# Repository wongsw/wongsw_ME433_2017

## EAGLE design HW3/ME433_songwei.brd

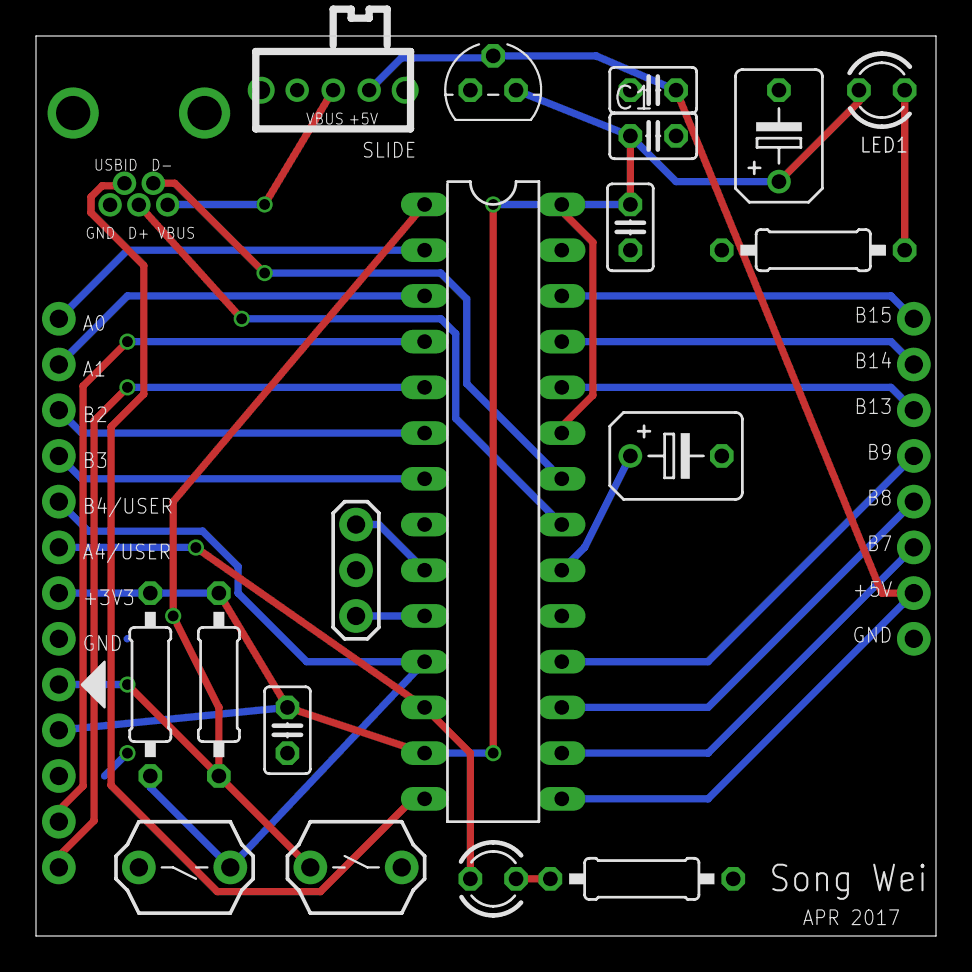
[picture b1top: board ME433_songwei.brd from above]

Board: 2 copper layers, 50.0 x 50.0 mm, 22 parts (0 on the bottom side), 27 nets.

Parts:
C1, C2, C3, C4: 0.1uF; C025-025X050
C5, C6: 10uF; B45181B
J1: USB-MB-H
LED1: Red; LED3MM
LED2: Green; LED3MM
R1, R2: 330; 0207/10
R3, R4: 10k; 0207/10
U$1: PIC32MX250F128B; DIL28-3
U$2: SLIDE
U$3: MCP1702; TO92
U$4: RESET; PB
U$5: USER; PB
U$6, U$7: CONN_08; 1X08
U$8: PICKIT3; 1X05
U$10: 8MHz; OSC

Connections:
+3V3: C1.1, C2.1, C4.1, C6.+, LED1.A, R3.2, R4.2, U$1.13, U$1.23, U$1.28, U$3.3, U$7.2, U$8.2
+5V: C3.1, U$1.15, U$2.3, U$3.2, U$6.2
A0: U$1.2, U$7.8
A1: U$1.3, U$7.7
A4/LED: LED2.A, U$1.12, U$7.3
B2: U$1.6, U$7.6
B3: U$1.7, U$7.5
B4/USER: R3.1, U$1.11, U$5.1, U$7.4
B7: U$1.16, U$6.3
B8: U$1.17, U$6.4
B9: U$1.18, U$6.5
B13: U$1.24, U$6.6
B14: U$1.25, U$6.7
B15: U$1.26, U$6.8
D+: J1.D+, U$1.21
D-: J1.D-, U$1.22
GND: C1.2, C2.2, C3.2, C4.2, C5.-, C6.-, J1.GND, R1.1, R2.1, U$1.8, U$1.19, U$1.27, U$3.1, U$4.2, U$5.2, U$6.1, U$7.1, U$8.3, U$10.2
MCLR: R4.1, U$1.1, U$4.1, U$8.1
unnamed: J1.VBUS, U$2.2
unnamed: U$1.9, U$10.1
unnamed: U$1.10, U$10.3
unnamed: C5.+, U$1.20
unnamed: LED1.K, R1.2
unnamed: LED2.K, R2.2
PGC: U$1.5, U$8.5
PGD: U$1.4, U$8.4
USBID: J1.ID, U$1.14

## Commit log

2017-03-28 :octocat: Added .gitattributes & .gitignore files
2017-03-28 My first commit!
2017-03-28 Added another line of code
2017-03-29 Added directories for installation files
2017-03-29 Added HW1: CIrcuit diagrams
2017-03-29 Added screenshots of 3.3V without/with capacitors
2017-03-29 Added picture of breadboard
2017-03-29 Created HW1 project on MPLAB IDE
2017-03-29 Added main.c file
2017-03-29 Updated pragma values and set up Green LED, button
2017-03-30 Added code to produce 1kHz square wave from LED
2017-03-30 Added HW1 Video
2017-03-30 Updated HW1 video
2017-03-30 minor changes to main.c
2017-04-04 Added .lbr, .sch and .brd files in HW2
2017-04-04 Worked on .brd and edited .sch
2017-04-05 Worked on PCB design in .brd file
2017-04-06 Updated .brd file, connections done
2017-04-06 Updated all silkscreen on .brd
2017-04-06 updated images in .brd
2017-04-06 Created Gerber files and zipped relevant files in HW3
2017-04-06 Updated HW3 folder
2017-04-11 Started code for SPI
2017-04-11 Added code to HW4
2017-04-11 Added DAC outputs screenshot and spi.c code
2017-04-11 Added DAC schematic and DAC output video
2017-04-13 Updated HW4 folder naming
2017-04-13 Created HW5 code
2017-04-13 Updated i2c files
2017-04-13 Working code for HW5
2017-04-13 Updated HW5 deliverables
2017-04-15 Started on HW6
2017-04-15 Updated HW1
2017-04-15 Updated HW 4
2017-04-15 Updated HW5
2017-04-15 Displayed test char
2017-04-15 Updated code to print string
2017-04-18 Updated HW6
2017-04-18 Updated Draw_bar()
2017-04-18 Completed HW6
2017-04-18 Updated HW6 deliverables
2017-04-19 Updated HW 6
2017-04-19 Started HW7
2017-04-20 WHO_AM_I reg read done
2017-04-20 Working on HW7
2017-04-20 Text reading from IMU done
2017-04-20 HW7 completed
2017-04-20 Updated HW7
2017-04-20 Created HW7 deliverables
2017-04-20 Added video in HW7 deliverables
2017-04-25 Created HW8
2017-04-25 Completed HW8
2017-04-25 Uploaded HW8 video
2017-04-26 Started HW9
2017-04-26 CDC state machine + USB libraries
2017-04-26 Printing out IMU values
2017-04-26 Included putty directory
2017-04-27 Completed HW9
2017-05-04 Updated till HW10
2017-05-04 Started HW11
2017-05-04 Completed HW11 code
2017-05-08 HW12 init commit
    App works on phone
2017-05-10 Completed HW12 code
    First Android App!
2017-05-10 HW13 init commit
2017-05-10 Working camera app
2017-05-11 Updated HW13 code
2017-05-16 Created HW14
2017-05-16 Created AndroidUSB app
2017-05-16 AndroidUSB app w/o USB
2017-05-16 Working AndroidUSB app
2017-05-16 Completed HW14
2017-05-16 HW14 Video added
2017-05-23 Uploaded CAD designs for wheels and box
2017-05-23 Uploaded wheel STL file for print
2017-05-23 Uploaded DXF file for laser cut
2017-06-05 HW 19 init commit
2017-06-05 Updated app
2017-06-05 Motor testing init
2017-06-06 Completed HW 18
2017-06-06 uploaded video
2017-06-09 Init commit
2017-06-09 Photo of 3D printed wheel
2017-06-09 Pictures of final robot
2017-06-09 Uploaded vid
